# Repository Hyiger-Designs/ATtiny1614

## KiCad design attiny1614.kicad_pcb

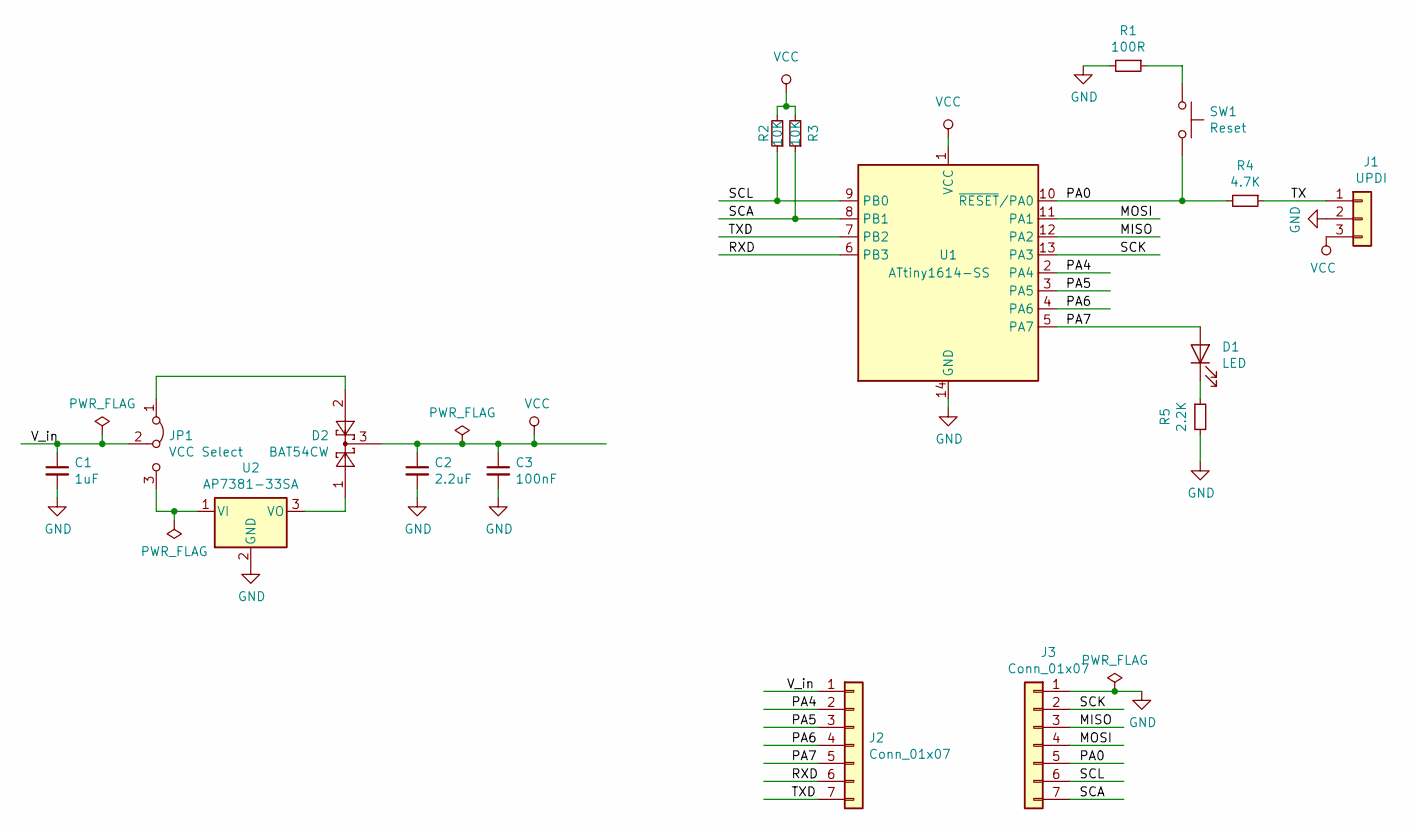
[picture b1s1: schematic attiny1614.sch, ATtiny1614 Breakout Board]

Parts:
C1: 1uF; C_0603_1608Metric_Pad1.05x0.95mm_HandSolder
C2: 2.2uF; C_0603_1608Metric_Pad1.05x0.95mm_HandSolder
C3: 100nF; C_0603_1608Metric_Pad1.05x0.95mm_HandSolder
D1: LED; LED_0603_1608Metric_Pad1.05x0.95mm_HandSolder
D2: BAT54CW; SOT-323_SC-70
J1: UPDI; PinHeader_1x03_P1.27mm_Vertical
J2, J3: Conn_01x07; PinHeader_1x07_P2.54mm_Vertical
JP1: VCC Select; PinHeader_1x03_P1.27mm_Vertical
R1: 100R; R_0603_1608Metric_Pad1.05x0.95mm_HandSolder
R2, R3: 10K; R_0603_1608Metric_Pad1.05x0.95mm_HandSolder
R4: 4.7K; R_0603_1608Metric_Pad1.05x0.95mm_HandSolder
R5: 2.2K; R_0603_1608Metric_Pad1.05x0.95mm_HandSolder
SW1: Reset; SW_Push_SPST_NO_Alps_SKRK
U1: ATtiny1614-SS; SOIC-14_3.9x8.7mm_P1.27mm
U2: AP7381-33SA; SOT-23

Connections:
/MISO: J3.3, U1.12 (PA2)
/MOSI: J3.4, U1.11 (PA1)
/PA0: J3.5, R4.2, SW1.2, U1.10 (~RESET~/PA0)
/PA4: J2.2, U1.2 (PA4)
/PA5: J2.3, U1.3 (PA5)
/PA6: J2.4, U1.4 (PA6)
/PA7: D1.2 (A), J2.5, U1.5 (PA7)
/RXD: J2.6, U1.6 (PB3)
/SCA: J3.7, R3.1, U1.8 (PB1)
/SCK: J3.2, U1.13 (PA3)
/SCL: J3.6, R2.1, U1.9 (PB0)
/TX: J1.1, R4.1
/TXD: J2.7, U1.7 (PB2)
/V_in: C1.1, J2.1, JP1.2 (C)
GND: C1.2, C2.2, C3.2, J1.2, J3.1, R1.2, R5.2, U1.14 (GND), U2.2 (GND)
unnamed: D2.1, U2.3 (VO)
unnamed: D2.2, JP1.1 (A)
unnamed: D1.1 (K), R5.1
unnamed: JP1.3 (B), U2.1 (VI)
unnamed: R1.1, SW1.1
VCC: C2.1, C3.1, D2.3, J1.3, R2.2, R3.2, U1.1 (VCC)

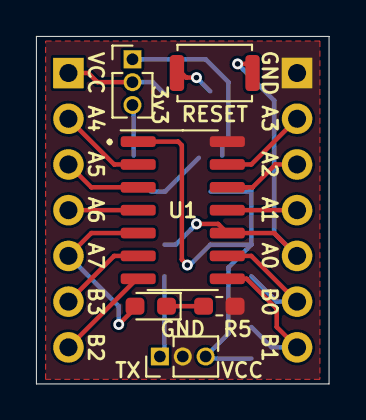
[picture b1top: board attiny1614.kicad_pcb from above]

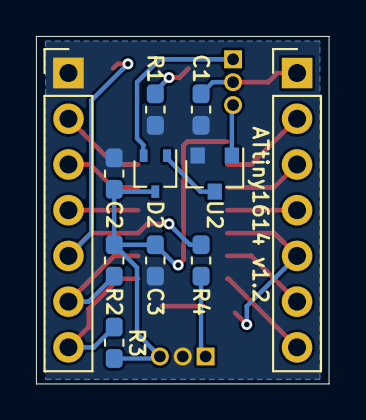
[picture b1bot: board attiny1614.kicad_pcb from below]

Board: 2 copper layers, 16.3 x 19.3 mm, 17 parts (11 on the bottom side), 21 nets.

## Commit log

2019-07-31 version 1.0
2019-07-31 removed mac files
2019-07-31 added led, generated gerbers
2019-08-07 gerbers and layout
